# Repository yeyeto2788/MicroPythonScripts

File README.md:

# MicroPythonScripts

Main repository of MicroPython projects and modules I have built on my spare time.

## Structure of the repository

- **`projects/<project_name>`**

  Folder containing everything related to the script.

  | Name      | Type          | Description                                                                                                 |
  | --------- | ------------- | ----------------------------------------------------------------------------------------------------------- |
  | `code`    | :file_folder: | Commented code for better understanding of it.                                                              |
  | `release` | :file_folder: | Code without comments and trying to be as small as possible in order to save memory on the microcontroller. |
  | `docs`    | :file_folder: | Files like images and so on for documentation purposes.                                                     |

- **`modules`**

  Folder containing everything related to MicroPython and some help classes and scripts to make deployments more easy.

  | Name       | Type          | Description                                                                                                 |
  | ---------- | ------------- | ----------------------------------------------------------------------------------------------------------- |
  | `code`     | :file_folder: | Commented code for better understanding of it.                                                              |
  | `release`  | :file_folder: | Code without comments and trying to be as small as possible in order to save memory on the microcontroller. |
  | `docs`     | :file_folder: | Files like images and so on for documentation purposes.                                                     |
  | `examples` | :file_folder: | Example files that in some cases will need to be renamed into `main.py` so it will be run at boot time.     |

- **`snipets`** :file_folder:

  Scripts used to saved some common code so I don't forget how to do some things.

- **`static`** :file_folder:

  Contains images for documentation purposes and other static files like HTML and CSS code.

- **`tools`** :file_folder:

  Tools used when developing within this repo.

- **`README.md`** :page_with_curl: on :file_folder:

  Documentation of the script, class or other important information.

---

## Project list

| Project name    | Status   | Link                                        |
| :-------------- | :------- | ------------------------------------------- |
| Bulleting board | **DONE** | [Get me there!](./projects/bulleting_board) |
| Camera slider   | **WIP**  | [Get me there!](./projects/camera_slider)   |
| Micro server    | **DONE** | [Get me there!](./projects/micro_server)    |
| Pomodoro        | **DONE** | [Get me there!](./projects/pomodoro)        |
| Problem solver  | **DONE** | [Get me there!](./projects/problem_solver)  |
| Script console  | **DONE** | [Get me there!](./projects/script_console)  |
| Weather display | **DONE** | [Get me there!](./projects/weather_display) |
| Weather station | **DONE** | [Get me there!](./projects/weather_station) |
| WiFi scanner    | **DONE** | [Get me there!](./projects/wifi_scan)       |

### Generating minified code:
I made a quick script to generate the commands to be executed in order to minify the code in the `projects` folder. Might overkill but sometimes in Windows it behaves different and having all commands at once comes in handy.

```console
python ./tools/generate_commands.py
chmod +x ./tools/obfuscate.sh
./tools/obfuscate.sh
```
---

<!-- Support -->

## Support :mechanic:

Reach out to me at one of the following places!

- Website at [juanbiondi.com](https://www.juanbiondi.com)
- Create an [issue](https://github.com/yeyeto2788/Things-Organizer/issues/new/choose) on this repository. :pirate_flag:
- Send me an [email](mailto:jebp.freelance@gmail.com) :email:

---

<!-- Contributing -->

## Contributing

Contributions are what make the open source community such an amazing place to be learn, inspire, and create. Any contributions you make are **greatly appreciated**.

1. Fork the Project
2. Create your Feature Branch (`git checkout -b feature/super_awesome_feature`)
3. Commit your Changes (`git commit -m 'Add some awesome feature'`)
4. Push to the Branch (`git push origin feature/super_awesome_feature`)
5. Open a Pull Request

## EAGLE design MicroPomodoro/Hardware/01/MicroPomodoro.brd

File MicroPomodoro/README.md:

# MicroPomodoro
This is a script that is used to implement the Pomodoro Technique, with a 25 mins working time and 5 mins break.

This uses the OLED LCD display on the board to show the remaining time, once the time finishes the alarm will go off.

What we need to do is download all the code from the **`Release`** folder and rename the **`pomodoro.py`** file to **`main.py`** so it will be executed after booting up.

## Parts needed:

  * ESP8266

  I'm using the Wemos D1 Mini board.

  * OLED display (I2C)

  * Buzzer

  * LEDs or Neopixel strip.

## Custom PCB for the project.
<p align="center">
<table align="center">
  <tr>
    <th>Version</th>
    <th>Top side of the board</th>
    <th>Placement of components</th>
    <th colspan="2">Comments</th>
  </tr>
  <tr>
    <td>Version 0.1</td>
    <td></td>
    <td></td>
    <td colspan="2">Use this version if you do not wish to use the OLED LCD display.</td>
  </tr>
  <tr>
    <td>Version 0.2</td>
    <td></td>
    <td></td>
    <td colspan="2">This version comes with 4 push buttons and 2 I2C connectors. You can see  <a href="./Doc/pdf/Schematics_v02.pdf">schematics</a> here.</td>
  </tr>
</table>
</p>

The idea with this board it not to have wires all over and also makes it better for fitting it into a 3D printed case (If anyone can help me out would be great) and also for connecting it to the Wemos D1 mini board.

 ~~I'll try to keep the design for single side PCB.~~ Since the price of making the PCBs is not that expensive, I decided to make it double sided to add more things on the board.

Eagle CAD files are within the **`Release`** folder

#### Bill of materials
<table align="center">
  <tr>
    <th>Item</th>
    <th>Quantity</th>
  </tr>
  <tr>
    <td>WS2812B Neopixel</td>
    <td>12</td>
  </tr>
  <tr>
    <td>100 pf Capacitor (SMD 1206)</td>
    <td>12</td>
  </tr>
  <tr>
    <td>SMD 1k Resistor (SMD 1206)</td>
    <td>4</td>
  </tr>
  <tr>
    <td>6mm Push button</td>
    <td>4</td>
  </tr>
  <tr>
    <td>Plain PCB (around 6x6 cm)</td>
    <td>1</td>
  </tr>
</table>

**The PCB is still in testing stage.** (Currently testing Version 0.2)

## Useful links:

[Pomodoro Technique](https://en.wikipedia.org/wiki/Pomodoro_Technique)

## TO DO:

- [ ] Add real execution image.

- [ ] Better documentation.

- [ ] Add buzzer ring alarm when finish.

- [ ] Add Eagle CAD design file, Gerber files and PDF for manual PCB manufacturing.
  <ul><li> - [x] Eagle Files</li>
  <li> - [ ] Gerber files.</li>
  <li> - [X] PDF files.</li></ul>

- [x] Add led or neopixel (Optional).

- [x] Add button execution.

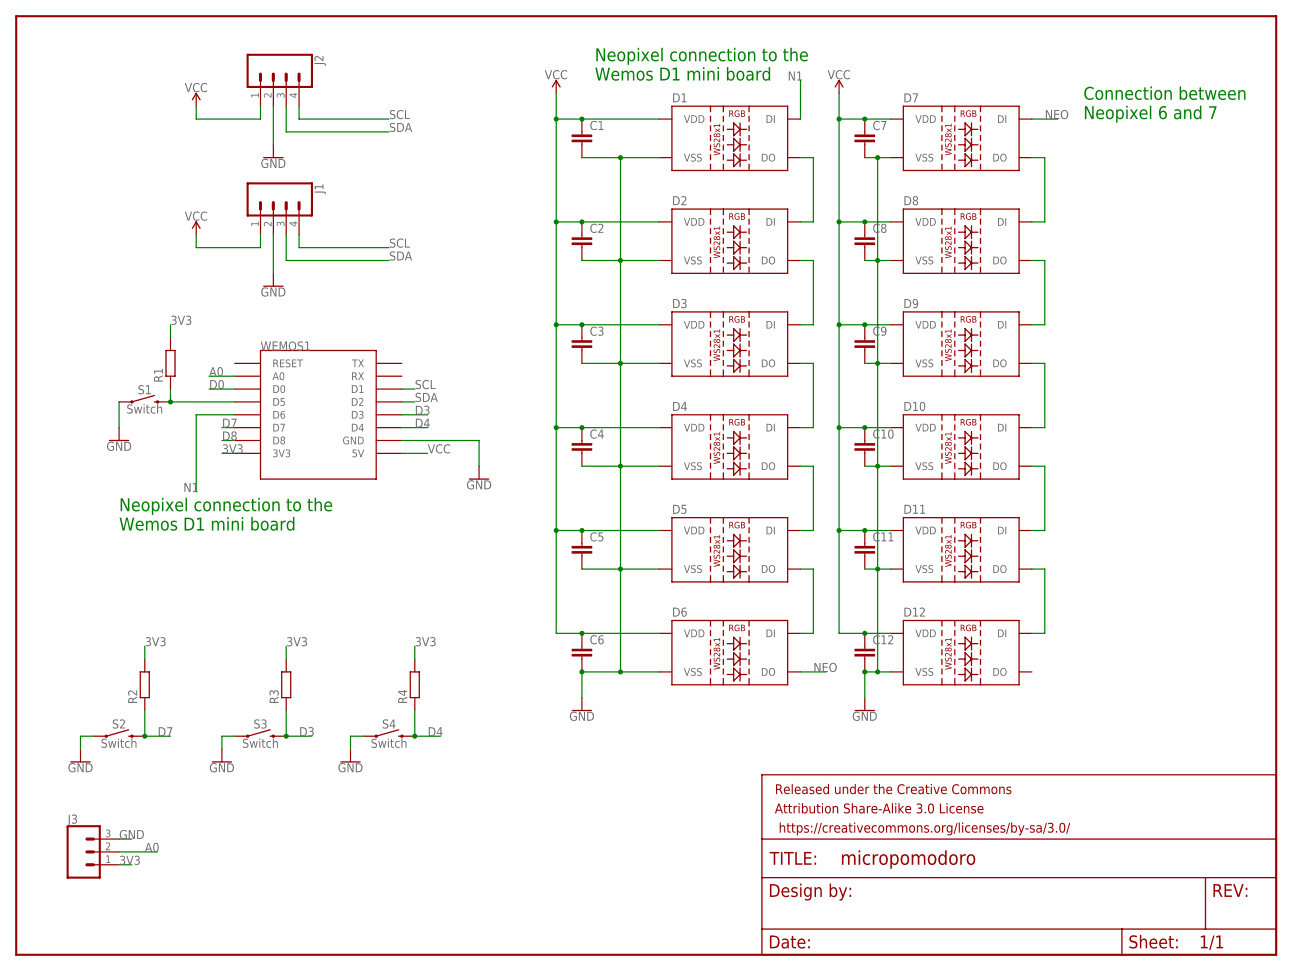
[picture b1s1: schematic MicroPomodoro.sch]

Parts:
C1, C2, C3, C4, C5, C6, C7, C8, C9, C10, C11, C12: CC1206; C1206
D1, D2, D3, D4, D5, D6, D7, D8, D9, D10, D11, D12: WS2812B
FRAME1: FRAME-LETTER; CREATIVE_COMMONS
J1: CONN_04LONGPADS; 1X04_LONGPADS
J2: CONN_04SMD_LONG; 1X04_SMD_LONG_NO_HOLE
J3: CONN_03SMD_RA_MALE; 1X03_SMD_RA_MALE
R1, R2, R3, R4: R-EU_R1206; R1206
S1, S2, S3, S4: Switch; TACTILE_SWITCH_PTH_6.0MM
WEMOS1: WEMOS-D1-MINI

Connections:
3V3: J3.1, R1.2, R2.2, R3.2, R4.2, WEMOS1.3V3
A0: J3.2, WEMOS1.A0
D0: WEMOS1.D0
D3: R3.1, S3.3 (2), WEMOS1.D3
D4: R4.1, S4.3 (2), WEMOS1.D4
D7: R2.1, S2.3 (2), WEMOS1.D7
D8: WEMOS1.D8
GND: C1.2, C2.2, C3.2, C4.2, C5.2, C6.2, C7.2, C8.2, C9.2, C10.2, C11.2, C12.2, D1.3 (VSS), D2.3 (VSS), D3.3 (VSS), D4.3 (VSS), D5.3 (VSS), D6.3 (VSS), D7.3 (VSS), D8.3 (VSS), D9.3 (VSS), D10.3 (VSS), D11.3 (VSS), D12.3 (VSS), J1.2, J2.2, J3.3, S1.1, S2.1, S3.1, S4.1, WEMOS1.GND
N1: D1.4 (DI), WEMOS1.D6
unnamed: R1.1, S1.3 (2), WEMOS1.D5
unnamed: D1.2 (DO), D2.4 (DI)
unnamed: D2.2 (DO), D3.4 (DI)
unnamed: D3.2 (DO), D4.4 (DI)
unnamed: D4.2 (DO), D5.4 (DI)
unnamed: D5.2 (DO), D6.4 (DI)
unnamed: D7.2 (DO), D8.4 (DI)
unnamed: D8.2 (DO), D9.4 (DI)
unnamed: D9.2 (DO), D10.4 (DI)
unnamed: D10.2 (DO), D11.4 (DI)
unnamed: D11.2 (DO), D12.4 (DI)
NEO: D6.2 (DO), D7.4 (DI)
SCL: J1.4, J2.4, WEMOS1.D1
SDA: J1.3, J2.3, WEMOS1.D2
VCC: C1.1, C2.1, C3.1, C4.1, C5.1, C6.1, C7.1, C8.1, C9.1, C10.1, C11.1, C12.1, D1.1 (VDD), D2.1 (VDD), D3.1 (VDD), D4.1 (VDD), D5.1 (VDD), D6.1 (VDD), D7.1 (VDD), D8.1 (VDD), D9.1 (VDD), D10.1 (VDD), D11.1 (VDD), D12.1 (VDD), J1.1, J2.1, WEMOS1.5V

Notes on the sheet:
Neopixel connection to the Wemos D1 mini board
Connection between Neopixel 6 and 7

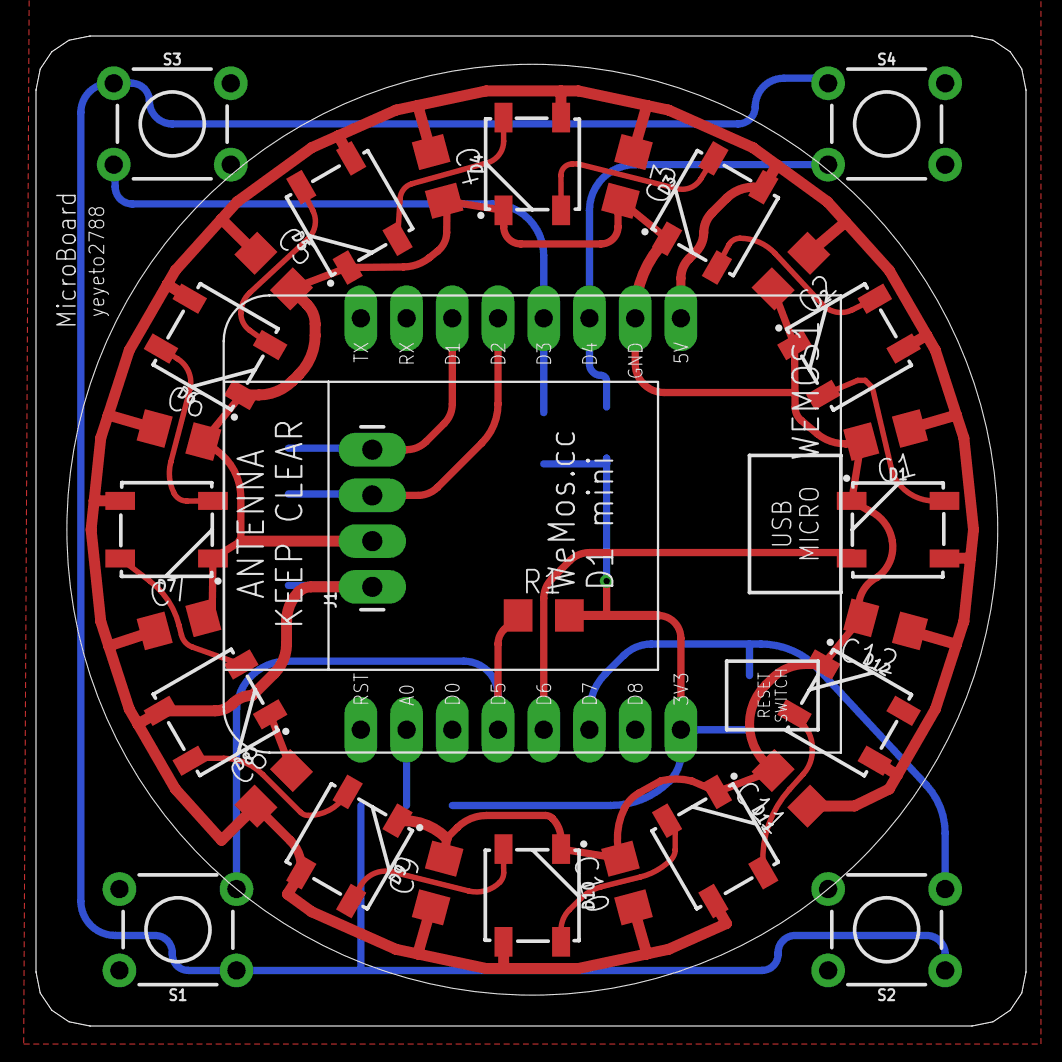
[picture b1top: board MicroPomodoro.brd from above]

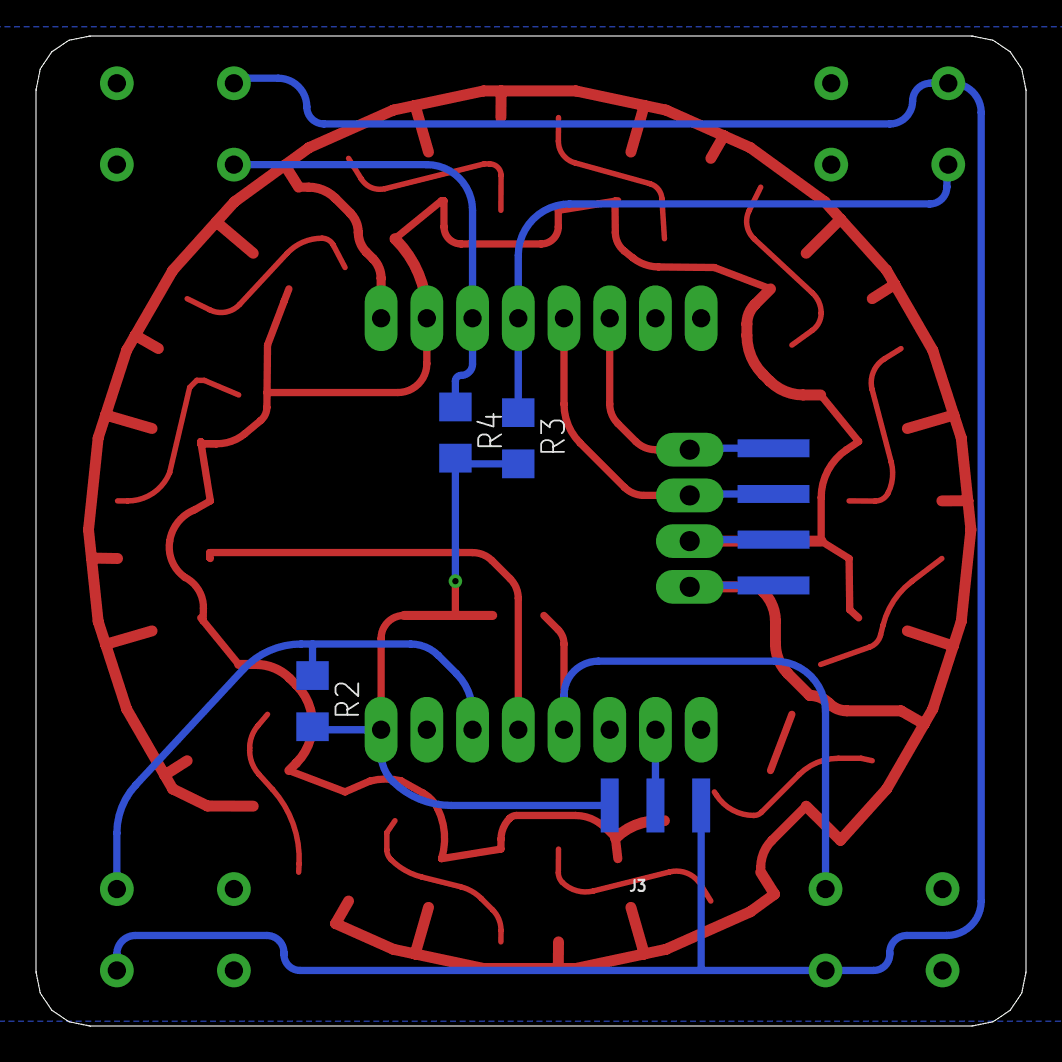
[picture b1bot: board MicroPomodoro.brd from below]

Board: 2 copper layers, 55.0 x 55.0 mm, 37 parts (5 on the bottom side), 22 nets.

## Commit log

2017-11-14 Rename WeatherThing/README.md to MicroWeatherThing/README.md
2017-11-14 Rename WeatherThing/Code/WeatherThing.py to MicroWeatherThing/Code/WeatherThing.py
2017-11-14 Rename WeatherThing/Release/WeatherThing.py to MicroWeatherThing/Release/WeatherThing.py
2017-11-14 Rename WeatherThing.py to MicroWeatherThing.py
2017-11-14 Rename HelpScripts/ConnectWiFi.py to HelpScripts/Code/ConnectWiFi.py
2017-11-15 Delete style.css
    With this script I wasn't able to get the file.
2017-11-15 Update MicroWeatherStation.py
    Add reload page every 15 mins
2017-11-15 Update MicroWeatherStation.py
    Add reload page every 15 segs
2017-11-15 Delete index.html
    No needed.
2017-11-15 Delete style.css
    No needed.
2018-01-15 Add new project
2018-03-06 Rearange items for quick find
2018-03-06 Remove items that were rearanged
2018-03-06 Add wifi manager class
2018-04-19 Add better execution of the code and delete not needed files.
2018-04-20 Fix some bugs on the code and add better execution
2018-04-20 Change doc image and fix a bit README file
2018-04-23 Add quick and dirty decode function.
2018-04-23 Fix quick and dirty decode function and add more characters to it.
2018-04-23 Fix indentation on folder description.
2018-04-24 Fix issue #2 where HTML is truncated
2018-04-24 Add sensor missing and todo tasks
2018-04-24 Add decode code for ñ letter
2018-05-02 Add basic CSS style on the HTML. Issue #4
2018-05-03 Add proporse solution for issue #5 and also add images of the board used.
2018-05-03 Change image on README for MicroBoard
2018-05-03 Add images to README and Doc folder
2018-05-14 Add custom PCB images and info on README
2018-05-14 Fix README errors
2018-05-17 Add error handling for OLED if not present and neopixel efects
2018-05-17 Add Eagle CAD, Schematic PDF files and change README
2018-05-25 Change style for HTML and add new picture of it.
2018-05-25 Add styling and error handling
2018-05-28 Add percentage symbol, add images and change readme.
2018-05-30 Add enhancement #10, lynt the code and update image.
2018-05-30 Add submodule to manage wifi.
2018-07-25 Move folder to where it belongs
2018-07-30 Add the uln2003 module.
2018-08-01 Fix issue #12 to uln2003 module
2018-08-01 Add example and document a bit more.
2018-08-01 Modify README
2018-08-01 Fix spelling
2018-08-08 Add new project MicroProblemSolver
2018-08-08 Fix typo on README
2018-08-09 Remove no needed script
2018-09-13 fix some typos
2018-09-13 Add MicroScriptConsole Module on the repo.
2018-10-02 Free memory on script while running.
2018-10-18 Add new scripts and make better code on old ones
2018-10-18 Fix execution and use same resources from the console module
2018-10-18 Change hex images to folder and rename some scripts
2018-10-18 Add img directory on call
2018-10-24 Add more info on README and tasks to be done.
2018-10-26 Firmware built, README for update, WIFI_sanner added
2018-10-31 Add new script and add info on README
2018-11-02 Add images on README, change code to work with time.tick_ms
2018-11-02 Fix some tipos on README
2018-11-02 Fix image size on README
2018-11-02 Add enhancement based on issue #3
2018-11-02 Add enhancement for issue #11
2018-12-03 Change folders directory and add new PythonScript folder
2019-02-04 Add more info and some needed files.
2019-02-04 Fix url on README
2019-03-21 Add MicroPomodoro hardware versions
2019-03-21 Add .gitignore file
2019-04-30 Rename file scripts and fix some typos code.
2019-04-30 Fix issue #14
2019-04-30 Beautify some help files.
2019-04-30 Fix some typos and lint issues on Modules
2019-05-02 Fix some typos and lint issues on Scripts
2019-05-09 Add some enhancements on the code in order to do extra work
2019-05-10 Add some enhancements on the code for CLI operations
2019-05-20 Add presentation skeleton
2019-05-20 Fix variable type for HelpScript > uncomment_and_upload, add .pylintrc file
2019-05-21 Add more info on slides and change some CSS.
2019-05-22 Add more info on slides and change some CSS part 2.
2019-05-23 Add more info on slides and change some CSS part 3.
2019-05-24 Rearrange presentation files and add waitress to requirements.
2019-05-24 Add requirements for whole repository
2019-05-24 Use f-strings on most part of the code and add ampy on requirements
2019-05-31 Add a few changes on the presentation
2019-06-04 Fix some lint issues.
2019-06-17 Fix some minor typos on timing and also ass option for one button boards
2019-06-17 Fix simple test to have a maximum of key presses
2019-06-18 Add "profile" image of mad scientist
2019-06-18 Add webcam view for the hands on part.
2019-07-18 Add possible image when no camera is detected and chanmge a bit the HTML image tags
2019-12-21 Bump waitress from 1.3.0 to 1.4.0
    Bumps [waitress](https://github.com/Pylons/waitress) from 1.3.0 to 1.4.0.
    - [Release notes](https://github.com/Pylons/waitress/releases)
    - [Changelog](https://github.com/Pylons/waitress/blob/master/CHANGES.txt)
    - [Commits](https://github.com/Pylons/waitress/compare/v1.3.0...v1.4.0)
2019-12-26 Bump waitress from 1.3.0 to 1.4.1
    Bumps [waitress](https://github.com/Pylons/waitress) from 1.3.0 to 1.4.1.
    - [Release notes](https://github.com/Pylons/waitress/releases)
    - [Changelog](https://github.com/Pylons/waitress/blob/master/CHANGES.txt)
    - [Commits](https://github.com/Pylons/waitress/compare/v1.3.0...v1.4.1)
2020-01-06 Bump waitress from 1.3.0 to 1.4.2
    Bumps [waitress](https://github.com/Pylons/waitress) from 1.3.0 to 1.4.2.
    - [Release notes](https://github.com/Pylons/waitress/releases)
    - [Changelog](https://github.com/Pylons/waitress/blob/master/CHANGES.txt)
    - [Commits](https://github.com/Pylons/waitress/compare/v1.3.0...v1.4.2)
2020-02-12 Bump waitress from 1.4.2 to 1.4.3
    Bumps [waitress](https://github.com/Pylons/waitress) from 1.4.2 to 1.4.3.
    - [Release notes](https://github.com/Pylons/waitress/releases)
    - [Changelog](https://github.com/Pylons/waitress/blob/master/CHANGES.txt)
    - [Commits](https://github.com/Pylons/waitress/compare/v1.4.2...v1.4.3)
2020-04-05 Add 3D designs for Hardware V02
2020-04-05 Make changes on code and config.json file in order to properly use the hardware V02
2020-04-05 Apply option to set a brightness for the neopixels on the code and based on the configuration in the config.json file.
2020-04-05 Add option to parse a given file instead of a whole directory and merge all requirements in a single file.
2020-04-05 Huge refactor of repository so we don't have several copies of the same file, reordering the structure of the repository.
2020-04-05 Change minor things on principal README.md
2020-04-09 Fix some snippets and add more snippets for simple operations.
2020-04-09 Fix typo on folder name.
2020-04-13 Add new project to the repo (Camera slider - WIP)
2020-04-14 Add tool to generate a zip file with all project/release files.
2020-04-14 Add more functions on the camera_slider project for further improvements.
2020-04-14 Do a quick refactor moving some variable on the tool for generating releases.
2020-11-30 Update DHT11.png
    A bit smaller picture
2020-11-30 Add better documentation for the repository
2020-11-30 Move dependencies to tools
    requirements.txt it is placed on tools dir since it is where it is being used.
2025-11-27 Update repo

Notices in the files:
parts and their libraries:
SparkFun-LED: Licensing: Creative Commons ShareAlike 4.0 International - https://creativecommons.org/licenses/by-sa/4.0
SparkFun-Retired: Released under the Creative Commons Attribution Share-Alike 3.0 License
SparkFun-Retired: https://creativecommons.org/licenses/by-sa/3.0
